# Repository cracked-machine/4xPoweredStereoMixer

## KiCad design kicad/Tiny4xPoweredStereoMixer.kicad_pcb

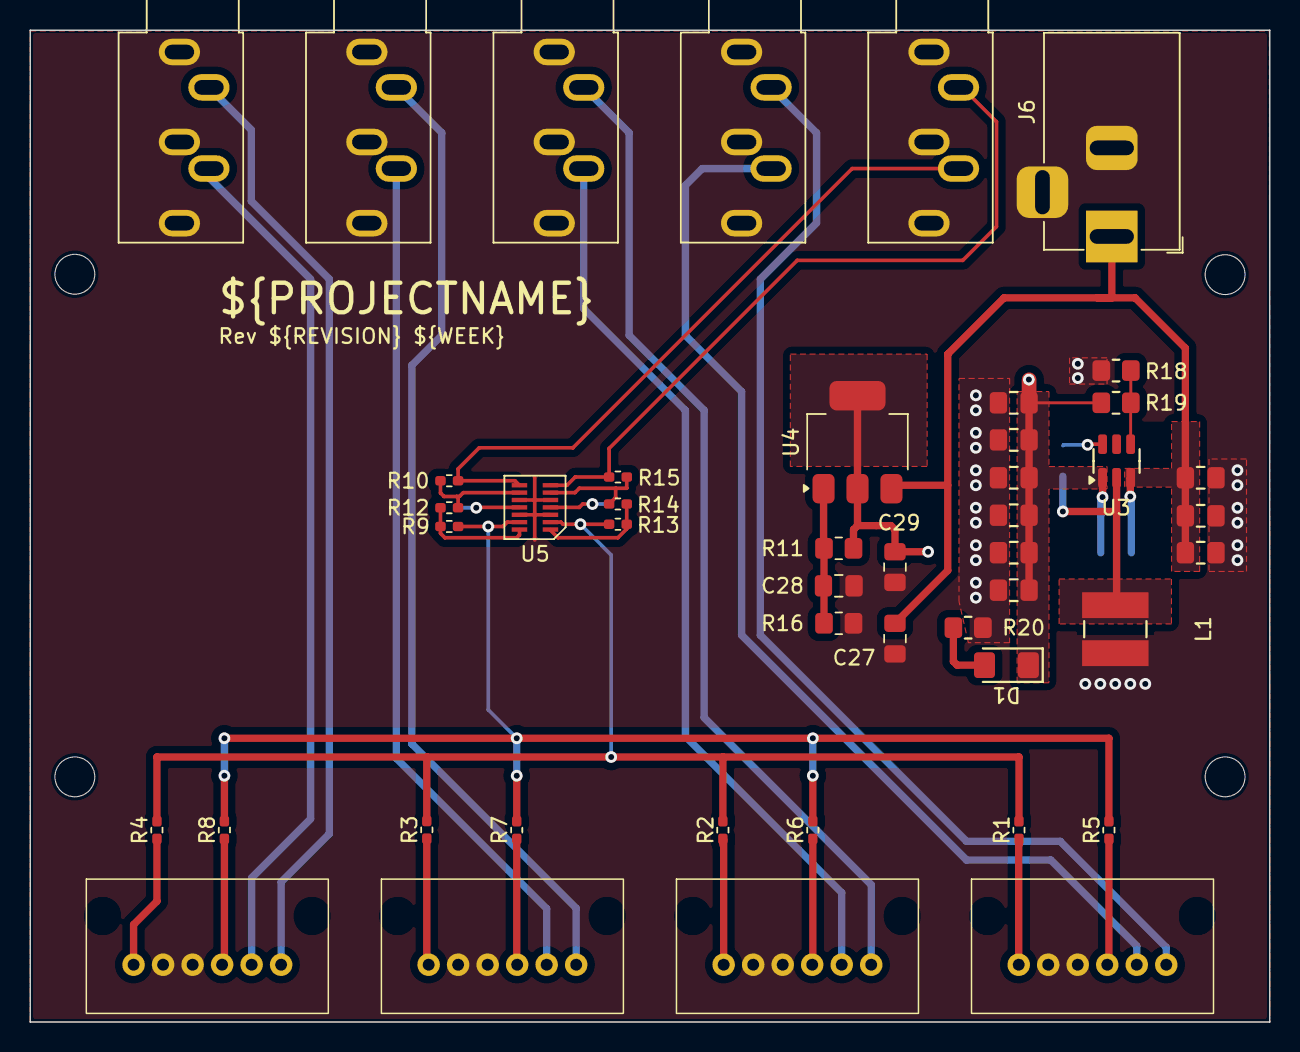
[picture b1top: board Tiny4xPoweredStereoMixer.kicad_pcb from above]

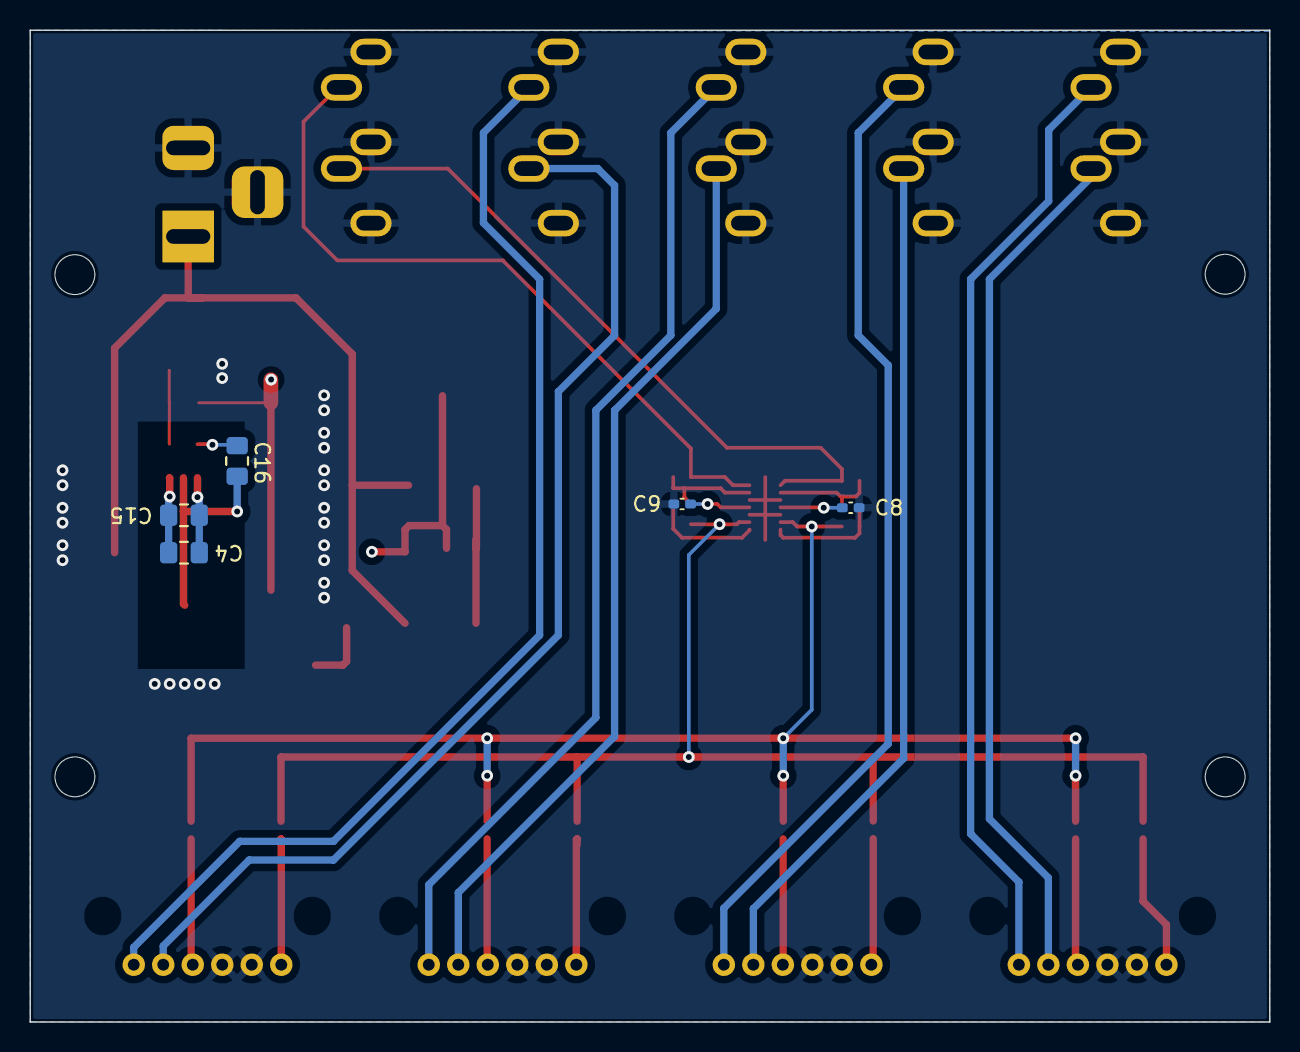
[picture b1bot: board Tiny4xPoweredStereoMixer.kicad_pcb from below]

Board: 4 copper layers, 84.0 x 67.2 mm, 55 parts (5 on the bottom side), 33 nets.

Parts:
C1, C2, C15, C27, C29: 10uF; C_0805_2012Metric_Pad1.18x1.45mm_HandSolder
C3, C4, C16, C21: 100nF; C_0805_2012Metric_Pad1.18x1.45mm_HandSolder
C8, C9: 100nF; C_0402_1005Metric_Pad0.74x0.62mm_HandSolder
C22, C23, C24, C25, C26, C28: 22uF; C_0805_2012Metric_Pad1.18x1.45mm_HandSolder
D1: LED; LED_1206_3216Metric_Pad1.42x1.75mm_HandSolder
H1, H2, H3, H4: MountingHole; MountingHole_2.7mm_M2.5
J1, J2, J3, J4, J9: AudioJack3_SwitchTR; Jack_3.5mm_CUI_SJ1-3535NG_Horizontal
J6: Barrel_Jack_Switch; BarrelJack_Horizontal
L1: 22uH; L_Ferrocore_DLG-0403
R1, R2, R3, R4, R5, R6, R7, R8, R9, R10, R12, R13, R14, R15: 10k; R_0402_1005Metric_Pad0.72x0.64mm_HandSolder
R11, R16: 120R; R_0805_2012Metric_Pad1.20x1.40mm_HandSolder
R18: 50K; R_0805_2012Metric_Pad1.20x1.40mm_HandSolder
R19: 2K4; R_0805_2012Metric_Pad1.20x1.40mm_HandSolder
R20: 2K2; R_0805_2012Metric_Pad1.20x1.40mm_HandSolder
RV1, RV2, RV3, RV4: 10k; Alps_RK12L12_Double_Horizontal
U3: TPS54202DDC; SOT-23-6
U4: LM1117MP-ADJ; SOT-223-3_TabPin2
U5: TL074; SOIC-14

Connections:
+2V5: C9.1, C29.1, R11.1, U4.2 (VO), U5.4 (V+)
+5V: C1.1, C2.1, C3.1, C4.1, C15.1, C27.1, J6.1, U3.3 (VIN), U4.3 (VI)
-2V5: C4.2, C8.1, C15.2, C21.2, C22.2, C23.2, C24.2, C25.2, C26.2, D1.1 (K), R19.1, U3.1 (GND), U5.11 (V-)
/TPS54202 Inverting PSU/VSENSE: R18.1, R19.2, U3.4 (FB)
/ch1_left_mix_in: R4.1, RV1.5
/ch1_right_mix_in: R8.1, RV1.2
/ch2_left_mix_in: R3.1, RV2.5
/ch2_right_mix_in: R7.1, RV2.2
/ch3_left_mix_in: R2.1, RV3.5
/ch3_right_mix_in: R6.1, RV3.2
/ch4_left_mix_in: R1.1, RV4.5
/ch4_right_mix_in: R5.1, RV4.2
GND: C1.2, C2.2, C3.2, C8.2, C9.2, C21.1, C22.1, C23.1, C24.1, C25.1, C26.1, C27.2, C28.2, C29.2, J1.RN, J1.S, J1.TN, J2.RN, J2.S, J2.TN, J3.RN, J3.S, J3.TN, J4.RN, J4.S, J4.TN, J6.2, J6.3, J9.RN, J9.S, J9.TN, L1.2, R16.2, R18.2, R20.2, RV1.1, RV1.4, RV2.1, RV2.4, RV3.1, RV3.4, RV4.1, RV4.4, U5.3 (+), U5.5 (+), U5.10 (+), U5.12 (+)
unnamed: D1.2 (A), R20.1
unnamed: J1.R, RV1.3
unnamed: J1.T, RV1.6
unnamed: J2.R, RV2.3
unnamed: J2.T, RV2.6
unnamed: J3.R, RV3.3
unnamed: J3.T, RV3.6
unnamed: J4.R, RV4.3
unnamed: J4.T, RV4.6
unnamed: J9.R, R10.2, U5.8
unnamed: J9.T, R15.2, U5.7
unnamed: R9.2, R12.1, U5.14
unnamed: R13.2, R14.1, U5.1
unnamed: C16.1, U3.6 (BOOT)
unnamed: C16.2, L1.1, U3.2 (SW)
unnamed: C28.1, R11.2, R16.1, U4.1 (ADJ)
unnamed: R1.2, R2.2, R3.2, R4.2, R13.1, U5.2 (-)
unnamed: R14.2, R15.1, U5.6 (-)
unnamed: R10.1, R12.2, U5.9 (-)
unnamed: R5.2, R6.2, R7.2, R8.2, R9.1, U5.13 (-)

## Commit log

2024-12-23 saving work in progress
2025-01-01 added gain calc pdfs
2025-01-01 tidied up psu, dac, mcu schematic
2025-01-02 Added RC networks to VCAs
